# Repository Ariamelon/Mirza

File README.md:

# Mirza
Current-feedback headphone amplifier module

## Disclaimer
This amplifier is licensed under CERN-OHL-S-2.0.

## Changelog
* 22/10/2024: License updated to CERN-OHL-S-2.0.
* 05/10/2023: Changed input voltage to 15V.
* 28/09/2023: Changed size of emitter resistors to MELF0207 for better heat dissipation.
* 24/09/2023: Increased thickness of power traces. Updated footprints for SOT-23-3 and SOT-23-6 footprints.
* 23/09/2023: Changed all dual transistors to BCM847DS/BCM857DS for easier soldering.
* 22/09/2023: Changed power connector to phoenix terminal block.
* 20/09/2023: Shortened board by removing one pair of capacitors and increasing the size of the other and reducing the number of emitter resistors.
* 18/09/2023: Changed power header to JST XH 6-pin.
* 17/09/2023: Repositioning of parts. Added interactive BOM. Changed some values. Removed PTC fuses. Lengthened board to add JST XH connectors.
* 16/09/2023: Initial public upload.

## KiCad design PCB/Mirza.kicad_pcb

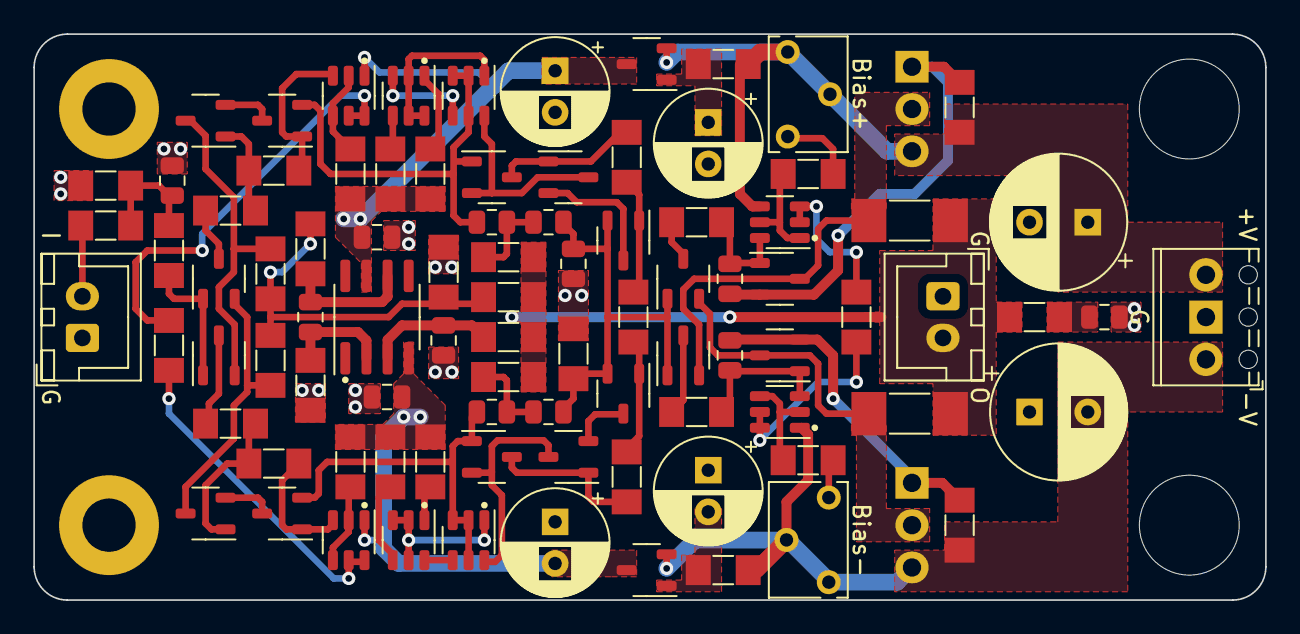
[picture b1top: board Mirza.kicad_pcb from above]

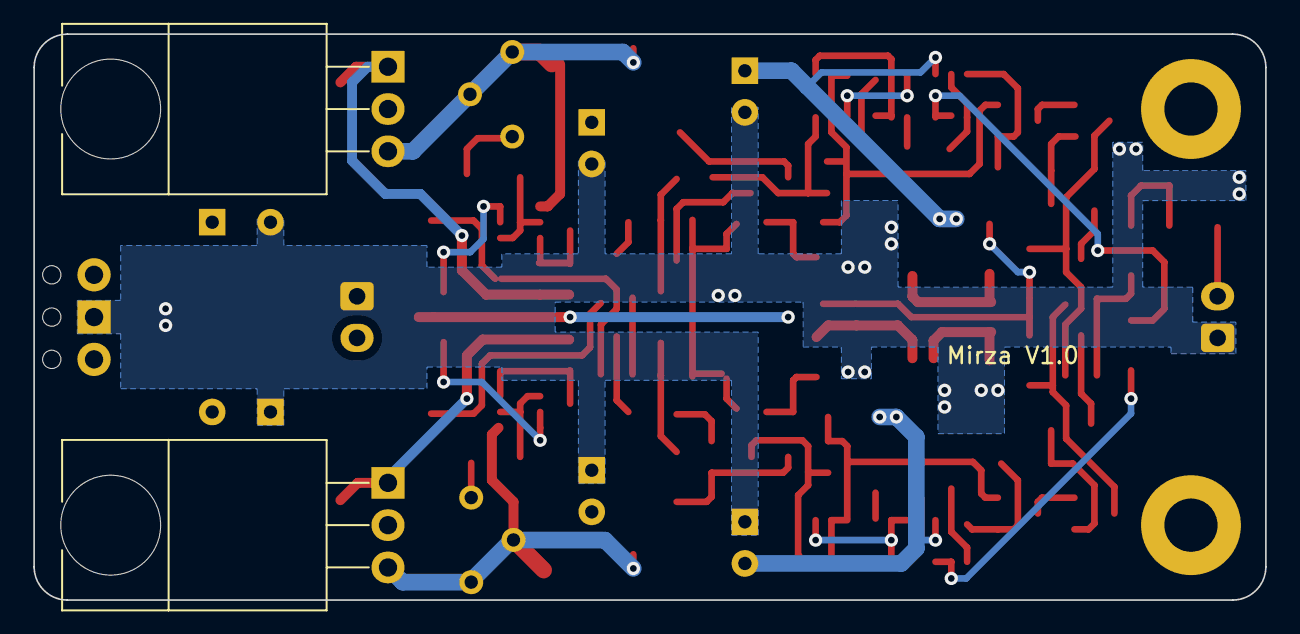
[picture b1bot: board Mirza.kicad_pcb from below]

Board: 2 copper layers, 74.0 x 34.0 mm, 95 parts (3 on the bottom side), 65 nets.

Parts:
A1: Ariamelon Logo; Ariamelon_Logo_Small_Mask
C1, C4, C5, C10, C11, C12: 100p; C_0805_2012Metric
C2, C3: 47p; C_0805_2012Metric
C6, C7, C8, C9: 100u; CP_Radial_D6.3mm_P2.50mm
C13: 10n; C_0805_2012Metric
C14, C15, C18, C19: 1u; C_0805_2012Metric
C16, C17: 470u; CP_Radial_D8.0mm_P3.50mm
H1, H2: M3; MountingHole_3.2mm_M3_Pad
J1: In; JST_XH_B2B-XH-A_1x02_P2.50mm_Vertical
J2: Out; JST_XH_B2B-XH-A_1x02_P2.50mm_Vertical
J3: Power; TerminalBlock_Phoenix_MPT-0,5-3-2.54_1x03_P2.54mm_Horizonta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
Q1, Q9, Q10, Q21: BCM857DS; SOT-23-6
Q2, Q11, Q12, Q22: BCM847DS; SOT-23-6
Q3, Q7, Q8, Q14, Q15, Q16, Q20, Q23, Q26: 2SA1312; SOT-23-3
Q4, Q5, Q6, Q13, Q17, Q18, Q19, Q24, Q25: 2SC3324; SOT-23-3
Q27: D45H11; TO-220-3_Horizontal_TabUp
Q28: D44H11; TO-220-3_Horizontal_TabUp
R1, R15, R16, R22, R23: 2k2; R_MiniMELF_MMA-0204
R2, R4, R25, R33: 10k; R_MiniMELF_MMA-0204
R3, R6, R7, R8, R9, R11, R12, R13, R14, R17, R21, R27, R28, R38: 68; R_MiniMELF_MMA-0204
R5, R10, R42: 560; R_MiniMELF_MMA-0204
R18, R20, R26, R29, R30, R31: 220; R_MiniMELF_MMA-0204
R19, R32: 100k; R_MiniMELF_MMA-0204
R24, R40: 1M; R_MiniMELF_MMA-0204
R36, R37: 0R47; R_MELF_MMB-0207
R43: 150; R_MiniMELF_MMA-0204
RV1, RV2: 1k; Potentiometer_Bourns_3266W_Vertical
U1: ADA4522-1; SOIC-8_3.9x4.9mm_P1.27mm

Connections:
+15V: C16.1, J3.3, Q19.2 (C), Q21.4 (E2), Q27.3 (E), R22.2, R30.2, RV1.1, RV1.2
-15V: C17.2, J3.1, Q20.2 (C), Q22.1 (E1), Q28.3 (E), R23.2, R31.2, RV2.1, RV2.2
Amp_FB: R12.2, R13.1, R33.1, R42.1, R43.2
Amp_Out: J2.2, R15.2, R16.2, R36.2, R37.2, R38.1, R40.2, R42.2
GND: C1.1, C6.2, C7.1, C8.1, C9.2, C10.2, C13.2, C14.2, C16.2, C17.1, C18.2, C19.1, J1.1, J2.1, J3.2, R2.2, R24.1, R32.2, R43.1
unnamed: C1.2, R1.2, R2.1, R3.1
unnamed: C2.2, C4.1, R15.1
unnamed: C3.2, C5.1, R16.1
unnamed: C13.1, R38.2
unnamed: C15.1, R33.2, U1.6
unnamed: J1.2, R1.1
unnamed: Q1.2 (B1), Q1.4 (E2), R5.1
unnamed: Q1.5 (B2), Q1.6 (C1), R4.1
unnamed: Q1.3 (C2), Q5.1 (B), R6.2
unnamed: Q2.2 (B1), Q2.4 (E2), R10.2
unnamed: Q2.5 (B2), Q2.6 (C1), R4.2
unnamed: Q2.3 (C2), Q8.1 (B), R9.2
unnamed: Q3.1 (B), Q4.1 (B), R3.2
unnamed: Q3.2 (C), Q7.3 (E), R13.2
unnamed: Q3.3 (E), R7.1
unnamed: Q4.2 (C), Q6.3 (E), R12.1
unnamed: Q4.3 (E), R8.1
unnamed: Q5.3 (E), Q6.2 (C)
unnamed: Q6.1 (B), R6.1, R7.2
unnamed: Q7.1 (B), R8.2, R9.1
unnamed: Q7.2 (C), Q8.3 (E)
unnamed: Q9.1 (E1), R17.2
unnamed: Q9.4 (E2), R11.1
unnamed: C2.1, Q5.2 (C), Q10.2 (B1), Q10.3 (C2), Q10.5 (B2), Q13.1 (B)
unnamed: Q10.6 (C1), Q13.2 (C), Q15.3 (E)
unnamed: Q9.2 (B1), Q9.5 (B2), Q9.6 (C1), Q10.1 (E1)
unnamed: Q9.3 (C2), Q10.4 (E2)
unnamed: C3.1, Q8.2 (C), Q11.2 (B1), Q11.3 (C2), Q11.5 (B2), Q14.1 (B)
unnamed: Q11.6 (C1), Q14.2 (C), Q18.3 (E)
unnamed: Q11.1 (E1), Q12.2 (B1), Q12.3 (C2), Q12.5 (B2)
unnamed: Q11.4 (E2), Q12.6 (C1)
unnamed: Q12.1 (E1), R14.2
unnamed: Q12.4 (E2), R21.2
unnamed: Q13.3 (E), Q15.1 (B), R18.1
unnamed: Q14.3 (E), Q18.1 (B), R20.2
unnamed: Q15.2 (C), Q16.3 (E)
unnamed: Q16.1 (B), R18.2, R19.1
unnamed: C4.2, C5.2, C10.1, Q16.2 (C), Q17.2 (C), Q23.1 (B), Q24.1 (B), R24.2
unnamed: Q17.1 (B), R19.2, R20.1
unnamed: Q17.3 (E), Q18.2 (C)
unnamed: C9.1, Q19.1 (B), R22.1
unnamed: C7.2, Q20.1 (B), R23.1
unnamed: Q21.2 (B1), Q21.3 (C2), R25.1
unnamed: C11.1, Q21.6 (C1), Q25.1 (B), R27.2
unnamed: Q21.1 (E1), Q21.5 (B2), R26.1
unnamed: Q22.2 (B1), Q22.4 (E2), R29.1
unnamed: Q22.5 (B2), Q22.6 (C1), R25.2
unnamed: C12.2, Q22.3 (C2), Q26.1 (B), R28.2
unnamed: Q23.2 (C), Q26.3 (E), Q28.2 (C), R37.1
unnamed: Q23.3 (E), R27.1
unnamed: Q24.2 (C), Q25.3 (E), Q27.2 (C), R36.1
unnamed: Q24.3 (E), R28.1
unnamed: C11.2, Q25.2 (C), Q27.1 (B), R30.1
unnamed: C12.1, Q26.2 (C), Q28.1 (B), R31.1
unnamed: R26.2, RV1.3
unnamed: R29.2, RV2.3
unnamed: C14.1, R40.1, U1.3 (+)
unnamed: C15.2, R32.1, U1.2 (-)
VCC: C6.1, C18.1, Q1.1 (E1), Q19.3 (E), R5.2, R11.2, R17.1, U1.7 (V+)
VEE: C8.2, C19.2, Q2.1 (E1), Q20.3 (E), R10.1, R14.1, R21.1, U1.4 (V-)

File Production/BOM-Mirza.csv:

Comment,Designator,Footprint,LCSC
1u,"C14,C15,C18,C19",C_0805_2012Metric,C126592
ADA4522-1,U1,SOIC-8_3.9x4.9mm_P1.27mm,C160794
10n,C13,C_0805_2012Metric,C161250
47p,"C2,C3",C_0805_2012Metric,C162302
470u,"C16,C17",CP_Radial_D8.0mm_P3.50mm,C178717
2k2,"R1,R15,R16,R22,R23",R_MiniMELF_MMA-0204,C1884620
560,"R10,R42,R5",R_MiniMELF_MMA-0204,C1884632
150,R43,R_MiniMELF_MMA-0204,C2074241
220,"R18,R20,R26,R29,R30,R31",R_MiniMELF_MMA-0204,C2074282
0R47,"R36,R37",R_MELF_MMB-0207,C2079987
10k,"R2,R25,R33,R4",R_MiniMELF_MMA-0204,C2084764
68,"R11,R12,R13,R14,R17,R21,R27,R28,R3,R38,R6,R7,R8,R9",R_MiniMELF_MMA-0204,C2086951
100u,"C6,C7,C8,C9",CP_Radial_D6.3mm_P2.50mm,C264049
100k,"R19,R32",R_MiniMELF_MMA-0204,C2836210
1M,"R24,R40",R_MiniMELF_MMA-0204,C4339242
BCM847DS,"Q11,Q12,Q2,Q22",SOT-23-6,C549558
BCM857DS,"Q1,Q10,Q21,Q9",SOT-23-6,C549564
100p,"C1,C10,C11,C12,C4,C5",C_0805_2012Metric,C710961
1k,"RV1,RV2",Potentiometer_Bourns_3266W_Vertical,C780233
2SC3324,Q5,SOT-23-3,
2SA1312,Q3,SOT-23-3,
2SC3324,Q18,SOT-23-3,
2SC3324,Q19,SOT-23-3,
2SA1312,Q16,SOT-23-3,
2SA1312,Q15,SOT-23-3,
Out,J2,JST_XH_B2B-XH-A_1x02_P2.50mm_Vertical,
2SA1312,Q23,SOT-23-3,
2SA1312,Q26,SOT-23-3,
2SA1312,Q8,SOT-23-3,
2SA1312,Q7,SOT-23-3,
2SC3324,Q6,SOT-23-3,
2SC3324,Q4,SOT-23-3,
2SC3324,Q13,SOT-23-3,
2SA1312,Q20,SOT-23-3,
Power,J3,"TerminalBlock_Phoenix_MPT-0,5-3-2.54_1x03_P2.54mm_Horizontal_MiddleGND",
2SC3324,Q17,SOT-23-3,
2SC3324,Q24,SOT-23-3,
In,J1,JST_XH_B2B-XH-A_1x02_P2.50mm_Vertical,
2SA1312,Q14,SOT-23-3,
2SC3324,Q25,SOT-23-3,
D45H11,Q27,TO-220-3_Horizontal_TabUp,
D44H11,Q28,TO-220-3_Horizontal_TabUp,

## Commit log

2023-09-14 Completed layout
2023-09-14 Update Ariamelon-Kicad-Master-Library
2023-09-16 Rearranged and rerouted board
2023-09-16 Initial public upload
2023-09-17 17/09/2023 update
    Repositioning of parts. Added interactive BOM. Changed some values. Removed PTC fuses. Lengthened board to add JST XH connectors.
2023-09-18 18/09/2023 update
    Changed power header to JST XH 6-pin.
2023-09-20 20/09/2023 update
    Shortened board by removing one pair of capacitors and increasing the size of the other and reducing the number of emitter resistors.
2023-09-22 22/03/2023 update
    Changed power connector to phoenix terminal block.
2023-09-23 23/09/2023 update
    Changed all dual transistors to BCM847DS/BCM857DS for easier soldering.
2023-09-24 24/09/2023 update
    Increased thickness of power traces. Updated footprints for SOT-23-3 and SOT-23-6 footprints.
2023-09-28 28/09/2023 update
    Changed size of emitter resistors to MELF0207 for better heat dissipation.
2023-10-05 05/10/2023 update
    Changed input voltage to 15V.
2024-10-22 License updated to CERN-OHL-S-2.0.

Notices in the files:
PCB/Mirza.kicad_pcb:
Licensed under CC BY 4.0.
